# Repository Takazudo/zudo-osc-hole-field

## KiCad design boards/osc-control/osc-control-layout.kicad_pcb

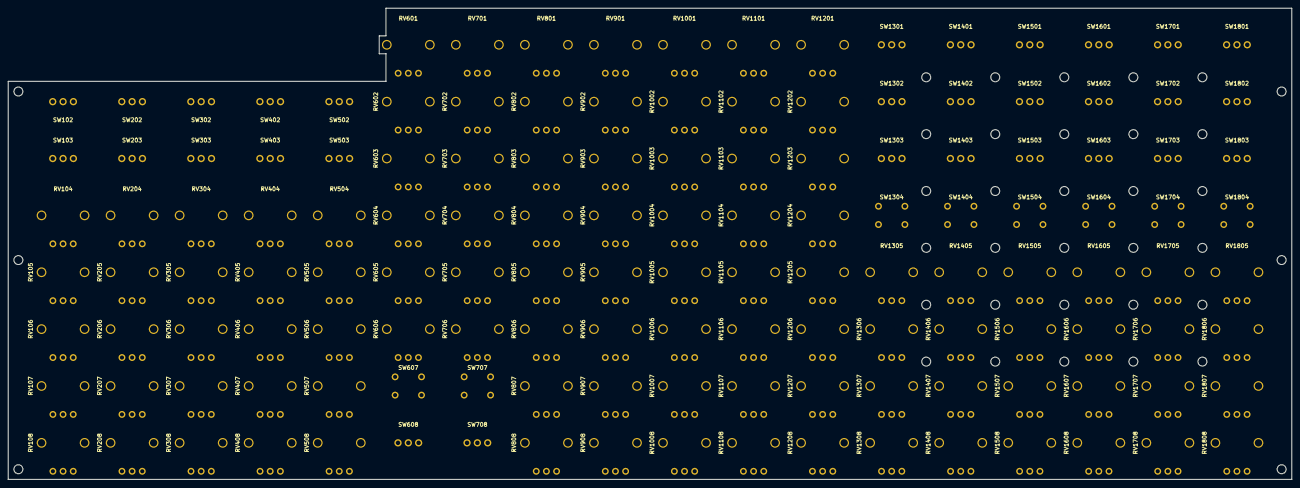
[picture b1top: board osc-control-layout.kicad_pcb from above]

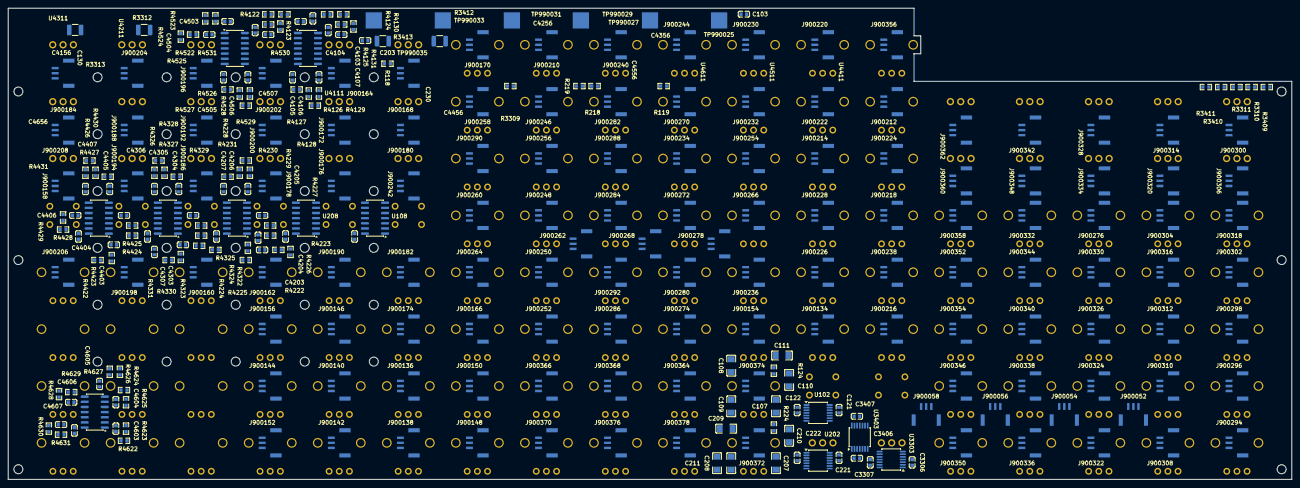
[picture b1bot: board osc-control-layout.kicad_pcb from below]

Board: 4 copper layers, 316.0 x 116.0 mm, 454 parts (279 on the bottom side), 348 nets, no tracks yet.

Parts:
C103, C203, C4104, C4105, C4106, C4107, C4204, C4205, C4206, C4207, C4304, C4305, C4306, C4307, C4404, C4405, C4406, C4407, C4504, C4505, C4506, C4507, C4604, C4605, C4606, C4607: 1e-07 F; C0603
C107, C108, C109, C110, C111, C207, C208, C209, C210, C211: 1e-07 F; C1206
C121, C122, C130, C221, C222, C230, C3306, C3307, C3406, C3407, C4156, C4256, C4356, C4456, C4556, C4656: 100 nF; C0603
C4103, C4203, C4303, C4403, C4503, C4603: 1 µF; C0603
J900052, J900054, J900056, J900058, J900134, J900136, J900138, J900140, J900142, J900144, J900146, J900148, J900150, J900152, J900154, J900156, J900158, J900160, J900162, J900164, J900166, J900168, J900170, J900172, J900174, J900176, J900178, J900180, J900182, J900184, J900186, J900188, J900190, J900192, J900194, J900196, J900198, J900200, J900202, J900204, J900206, J900208, J900210, J900212, J900214, J900216, J900218, J900220, J900222, J900224, J900226, J900228, J900230, J900232, J900234, J900236, J900238, J900240, J900242, J900244, J900246, J900248, J900250, J900252, J900254, J900256, J900258, J900260, J900262, J900264, J900266, J900268, J900270, J900272, J900274, J900276, J900278, J900280, J900282, J900284, J900286, J900288, J900290, J900292, J900294, J900296, J900298, J900300, J900302, J900304, J900306, J900308, J900310, J900312, J900314, J900316, J900318, J900320, J900322, J900324, J900326, J900328, J900330, J900332, J900334, J900336, J900338, J900340, J900342, J900344, J900346, J900348, J900350, J900352, J900354, J900356, J900358, J900360, J900362, J900364, J900366, J900368, J900370, J900372, J900374, J900376, J900378: BM03B-GHS-TBT(LF)(SN); JST_GH3_BM_TopEntry
MH_P-OPT-2, MH_P-OPT-3, MH_P-OPT-4, MH_P-OPT-5, MH_P-OPT-6, MH_P-OPT-7, MH_P-OPT-9, MH_P-OPT-10, MH_P-OPT-11, MH_P-OPT-12, MH_P-OPT-13, MH_P-OPT-14, MH_P-OPT-16, MH_P-OPT-17, MH_P-OPT-18, MH_P-OPT-19, MH_P-OPT-20, MH_P-OPT-21, MH_P-OPT-23, MH_P-OPT-24, MH_P-OPT-25, MH_P-OPT-26, MH_P-OPT-27, MH_P-OPT-28, MH_P-OPT-30, MH_P-OPT-31, MH_P-OPT-32, MH_P-OPT-33, MH_P-OPT-34, MH_P-OPT-35: NPTH mounting hole
MH_P-SUP-1, MH_P-SUP-2, MH_P-SUP-3, MH_P-SUP-4, MH_P-SUP-5, MH_P-SUP-6: NPTH mounting hole
R118, R218, R4122, R4124, R4126, R4128, R4130, R4222, R4224, R4226, R4228, R4230, R4322, R4324, R4326, R4328, R4330, R4422, R4424, R4426, R4428, R4430, R4522, R4524, R4526, R4528, R4530, R4622, R4624, R4626, R4628, R4630: 10000 Ω; R0603
R119, R219, R4123, R4125, R4127, R4129, R4131, R4223, R4225, R4227, R4229, R4231, R4323, R4325, R4327, R4329, R4331, R4423, R4425, R4427, R4429, R4431, R4523, R4525, R4527, R4529, R4531, R4623, R4625, R4627, R4629, R4631: 1000 Ω; R0603
R124, R224: 2200 Ω; R0603
R3309, R3310, R3409, R3410: 2.2 kΩ; R0603
R3311, R3411: 10 MΩ; R0603
R3312, R3313, R3412, R3413: 499 Ω; R_1210_3225Metric
RV104, RV105, RV107, RV204, RV205, RV207, RV304, RV305, RV307, RV404, RV405, RV407, RV504, RV505, RV507, RV601, RV602, RV605, RV701, RV702, RV705, RV801, RV802, RV805, RV907, RV908, RV1106, RV1107, RV1108, RV1206, RV1305, RV1306, RV1308, RV1405, RV1406, RV1408, RV1505, RV1506, RV1508, RV1605, RV1606, RV1608, RV1705, RV1706, RV1708, RV1805, RV1806, RV1808: PTV09A-4020F-B104; PTV09A-4020F
RV106, RV108, RV206, RV208, RV306, RV308, RV406, RV408, RV506, RV508, RV603, RV604, RV606, RV703, RV704, RV706, RV803, RV804, RV806, RV901, RV902, RV903, RV904, RV905, RV906, RV1001, RV1002, RV1003, RV1004, RV1005, RV1006, RV1007, RV1008, RV1101, RV1102, RV1103, RV1104, RV1105, RV1201, RV1202, RV1203, RV1204, RV1205, RV1207, RV1208, RV1307, RV1407, RV1507, RV1607, RV1707, RV1807: PTV09A-4020F-B103; PTV09A-4020F
RV807, RV808: PTV09A-4020F-B504; PTV09A-4020F
SW102, SW202, SW302, SW402, SW502, SW608, SW708, SW1302, SW1303, SW1402, SW1403, SW1502, SW1503, SW1602, SW1603, SW1702, SW1703, SW1802, SW1803: 2MS1T1B1M2QES-5; Toggle_Dailywell_2MS_T1B1M2
SW103, SW203, SW303, SW403, SW503, SW1301, SW1401, SW1501, SW1601, SW1701, SW1801: 2MS3T1B1M2QES; Toggle_Dailywell_2MS_T1B1M2
SW607, SW707, SW1304, SW1404, SW1504, SW1604, SW1704, SW1804: B3F-1020; Button_Omron_B3F_6x6_P6.5x4.5
TP990025, TP990027, TP990029, TP990031, TP990033, TP990035: LOAD WIRE SOLDER LAND; LoadWireTerminal_4x4mm
U102, U202, U3303, U3403: OPA4197IPWR; TSSOP-14_4.4x5mm_P0.65mm
U108, U208, U4111, U4211, U4311, U4411, U4511, U4611: SN74HC14DR; SOIC-14_3.9x8.7mm_P1.27mm

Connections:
+5V: C130.1, C230.1, C4156.1, C4256.1, C4356.1, C4456.1, C4556.1, C4656.1, R118.1, R218.1, R4122.1, R4124.1, R4126.1, R4128.1, R4130.1, R4222.1, R4224.1, R4226.1, R4228.1, R4230.1, R4322.1, R4324.1, R4326.1, R4328.1, R4330.1, R4422.1, R4424.1, R4426.1, R4428.1, R4430.1, R4522.1, R4524.1, R4526.1, R4528.1, R4530.1, R4622.1, R4624.1, R4626.1, R4628.1, R4630.1, TP990029.1, U108.14, U208.14, U4111.14, U4211.14, U4311.14, U4411.14, U4511.14, U4611.14
+12V: C122.1, C222.1, C3306.1, C3406.1, TP990025.1, U102.4, U202.4, U3303.4, U3403.4
-12V: C121.1, C221.1, C3307.1, C3407.1, TP990027.1, U102.11, U202.11, U3303.11, U3403.11
AGND: C103.2, C107.2, C108.2, C109.2, C110.2, C111.2, C121.2, C122.2, C130.2, C203.2, C207.2, C208.2, C209.2, C210.2, C211.2, C221.2, C222.2, C230.2, C3306.2, C3307.2, C3406.2, C3407.2, C4103.2, C4104.2, C4105.2, C4106.2, C4107.2, C4156.2, C4203.2, C4204.2, C4205.2, C4206.2, C4207.2, C4256.2, C4303.2, C4304.2, C4305.2, C4306.2, C4307.2, C4356.2, C4403.2, C4404.2, C4405.2, C4406.2, C4407.2, C4456.2, C4503.2, C4504.2, C4505.2, C4506.2, C4507.2, C4556.2, C4603.2, C4604.2, C4605.2, C4606.2, C4607.2, C4656.2, J900052.2, J900054.2, J900056.2, J900058.2, J900134.2, J900136.2, J900138.2, J900140.2, J900142.2, J900144.2, J900146.2, J900148.2, J900150.2, J900152.2, J900154.2, J900156.2, J900158.2, J900160.2, J900162.2, J900164.2, J900166.2, J900168.2, J900170.2, J900172.2, J900174.2, J900176.2, J900178.2, J900180.2, J900182.2, J900184.2, J900186.2, J900188.2, J900190.2, J900192.2, J900194.2, J900196.2, J900198.2, J900200.2, J900202.2, J900204.2, J900206.2, J900208.2, J900210.2, J900212.2, J900214.2, J900216.2, J900218.2, J900220.2, J900222.2, J900224.2, J900226.2, J900228.2, J900230.2, J900232.2, J900234.2, J900236.2, J900238.2, J900240.2, J900242.2, J900244.2, J900246.2, J900248.2, J900250.2, J900252.2, J900254.2, J900256.2, J900258.2, J900260.2, J900262.2, J900264.2, J900266.2, J900268.2, J900270.2, J900272.2, J900274.2, J900276.2, J900278.2, J900280.2, J900282.2, J900284.2, J900286.2, J900288.2, J900290.2, J900292.2, J900294.2, J900296.2, J900298.2, J900300.2, J900302.2, J900304.2, J900306.2, J900308.2, J900310.2, J900312.2, J900314.2, J900316.2, J900318.2, J900320.2, J900322.2, J900324.2, J900326.2, J900328.2, J900330.2, J900332.2, J900334.2, J900336.2, J900338.2, J900340.2, J900342.2, J900344.2, J900346.2, J900348.2, J900350.2, J900352.2, J900354.2, J900356.2, J900358.2, J900360.2, J900362.2, J900364.2, J900366.2, J900368.2, J900370.2, J900372.2, J900374.2, J900376.2, J900378.2, R3311.2, R3411.2, RV106.1, RV107.1, RV108.1, RV206.1, RV207.1, RV208.1, RV306.1, RV307.1, RV308.1, RV406.1, RV407.1, RV408.1, RV506.1, RV507.1, RV508.1, RV601.1, RV602.1, RV603.1, RV604.1, RV605.1, RV606.1, RV701.1, RV702.1, RV703.1, RV704.1, RV705.1, RV706.1, RV801.1, RV802.1, RV803.1, RV804.1, RV805.1, RV806.1, RV901.1, RV902.1, RV903.1, RV904.1, RV905.1, RV906.1, RV907.1, RV1001.1, RV1002.1, RV1003.1, RV1004.1, RV1005.1, RV1006.1, RV1007.1, RV1008.1, RV1101.1, RV1102.1, RV1103.1, RV1104.1, RV1105.1, RV1106.1, RV1107.1, RV1201.1, RV1202.1, RV1203.1, RV1204.1, RV1205.1, RV1206.1, RV1207.1, RV1208.1, RV1305.1, RV1306.1, RV1307.1, RV1405.1, RV1406.1, RV1407.1, RV1505.1, RV1506.1, RV1507.1, RV1605.1, RV1606.1, RV1607.1, RV1705.1, RV1706.1, RV1707.1, RV1805.1, RV1806.1, RV1807.1, SW102.1, SW202.1, SW302.1, SW402.1, SW502.1, SW607.1, SW607.2, SW707.1, SW707.2, SW1301.2, SW1302.2, SW1303.2, SW1304.1, SW1304.2, SW1401.2, SW1402.2, SW1403.2, SW1404.1, SW1404.2, SW1501.2, SW1502.2, SW1503.2, SW1504.1, SW1504.2, SW1601.2, SW1602.2, SW1603.2, SW1604.1, SW1604.2, SW1701.2, SW1702.2, SW1703.2, SW1704.1, SW1704.2, SW1801.2, SW1802.2, SW1803.2, SW1804.1, SW1804.2, TP990031.1, TP990033.1, TP990035.1, U102.10, U102.12, U108.3, U108.5, U108.7, U108.9, U108.11, U108.13, U202.10, U202.12, U208.3, U208.5, U208.7, U208.9, U208.11, U208.13, U3303.5, U3303.10, U3303.12, U3403.5, U3403.10, U3403.12, U4111.7, U4111.13, U4211.7, U4211.13, U4311.7, U4311.13, U4411.7, U4411.13, U4511.7, U4511.13, U4611.7, U4611.13
X0B4A0A5D45814E9D95C7: U3303.13, U3303.14
X0B332CC3F3D75834394B: J900344.1, RV404.3, RV405.3, RV407.3
X0B475DAB16A59C025E35: J900170.1, U4111.10
X0C487389EDA1C803A833: J900304.3, SW102.2
X00D3BCB5E0AFD29A84DF: J900314.1, SW203.1
X0E3CA1A11E5FE92DB152: J900242.1, U108.2
X0F98EC836B304857ABC5: C4404.1, R4425.2, U4411.3
X01A05DBEFB68471D9824: J900186.1, U4311.10
X1A9EF65F44F4B29DE1DC: J900368.1, RV1207.3
X1B3E855D0EAF37C63927: J900326.3, RV306.3
X1B80C209713652D469B7: J900328.3, SW302.3
X1B787BB4D565EE8CF824: R4226.2, R4227.1, SW1401.3
X1C49E274E70449E3D265: R3309.2, SW608.3
X1C545F78A9EEA47275D3: J900148.3, RV1608.2
X1CB7E660D7B486B8C4E6: J900056.1, R3313.2
X1D7C13EF0F0429C157CA: J900212.3, RV603.2
X1DA6F66C3F8A34A27A5F: U3403.6, U3403.7
X1DA464D505A944A51104: J900360.1, RV508.3
X1E5E726E8BFBF2C8D7CB: J900198.3, RV1706.2
X1EA7A310545B3EA7B872: C4603.1, R4623.2, U4611.1
X1F3BE2B0C54B7392AAD2: J900214.1, RV602.2
X1FFDC49339C7C2982F1A: J900256.1, RV1102.2
X2B2FD6CD1D1554A8B31B: J900164.1, U4111.4
X2BCD7805C65AE3992EDF: R4628.2, R4629.1, SW1802.3
X2CA281339CB17909B79A: J900332.1, RV308.3
X02CB8FF55279DAA45A09: J900196.1, U4511.4
X2D597327EED2D1A7509E: J900162.3, RV1808.1
X2DAE1746253A01B64F3C: J900346.1, RV408.3
X2F4053E8598569E6249E: J900362.3, SW503.2
X3A090CBB9D59BF6BFA74: C103.1, R119.2, U108.1
X3AACF3FE67214DD30896: R4422.2, R4423.1, SW1604.3, SW1604.4
X3B8BA61DD852C09F9593: J900182.1, RV1505.2
X3B24EF7B17B8D143C1C5: J900058.3, R3413.2
X3BE215420217265BBCC4: J900330.3, RV304.1, RV305.1
X3C4EB2F54BEF66A2BDCD: J900372.1, RV908.2
X3C30CF4F46CC9EAA54FD: C4405.1, R4427.2, U4411.5
X3CB093BB7419E86B97DC: J900198.1, RV1705.2
X3D9DB9D8CDF65F493A37: J900208.1, U4611.6
X3DAC76D7A558264A3F1B: J900260.3, RV1204.3
X3F9931ACD1A8A527BDB6: J900274.3, RV906.2
X3FCBFC999FCAA257D324: R4622.2, R4623.1, SW1804.3, SW1804.4
X4AD789F56C4006DE7DA9: J900264.1, RV1206.2
X4C73DFC1A892FFD889F5: C4205.1, R4227.2, U4211.5
X4E9DA5171986B7A73694: J900292.1, RV1004.2
X04EB6B3DC069E08BFECF: J900310.3, RV207.2
X4F82C77EF7F47F31A68A: J900306.3, SW103.2
X5AC892F0D8CDA44E7E18: J900322.3, RV308.2
X05B3B6DFB0CF591143F1: J900374.1, RV907.2
X5BC1C28EAF5D67603036: J900340.3, RV406.3
X5BDE0CC9A020C6F2E113: J900136.3, RV1308.3
X5E1E2BAA433858C2BF43: U202.8, U202.9
X5EE2EC8E69809DDC2E3E: C4306.1, R4329.2, U4311.9
X5FA328E898DBF1047AD9: J900140.3, RV1407.3
X06C7F5D4F085BBED1E86: J900370.3, RV1108.1
X6C227D1A4FFD615CE3B4: J900152.1, RV1608.3
X6EAF3E6A330509674504: R4426.2, R4427.1, SW1601.3
X6F1E82B9DD7E6011E5A7: U3403.8, U3403.9
X7B5C74E08F15CF029DD6: J900256.3, RV1106.3
X7B7BDD1C1DB4BA20302F: C4106.1, R4129.2, U4111.9
X7B6418A02124BE1D6A53: J900346.3, SW402.2
X7CA4825DF75BA1068B88: J900312.3, RV206.3
X7DF116D877C176D3E3C1: R4230.2, R4231.1, SW1403.3
X7EC00F55D7B5A706ABE8: J900160.1, RV1807.2
X7EED3C2496125C7B4C01: J900226.3, RV704.2
X7FF164FB414EE3E69E00: J900348.1, SW403.3
X8A7D7D29E8DC52F3CE4A: J900206.1, RV1805.2
X8A58565164C7AD5DB771: J900210.3, U4611.2
X08AB1FE396D2383E44F4: J900210.1, U4611.10
X8B9429ACCBF48C55D3C2: C4607.1, R4631.2, U4611.11
X8BE7E102E23D65C3BAE8: C4304.1, R4325.2, U4311.3
X8D47F4038AE6E42915B2: J900300.3, SW102.3
X8D097FC3EE080878BFAC: J900234.3, RV805.2
X8EE69A8E59E4947794DE: R224.2, RV808.1
X8F338CC60323B9942D2C: C4103.1, R4123.2, U4111.1
X8FFBDC9C42EC02C29B2F: J900278.1, RV902.2
X9A2A689D1C741BE6AFED: J900280.1, RV904.2
X9A343D229ADA66A13020: J900176.3, RV1405.3, RV1406.3
X9A815A035049F63C9E88: J900244.1, U208.2
X9B0D87C92BF046274E53: U202.13, U202.14
X9C285D3C07BA239ADB72: J900324.3, RV307.2
X9D8BBA8996899EAF9E11: R4424.2, R4425.1, SW1601.1
X9D084A84DCD90DC3DD20: R218.2, R219.1, SW707.3, SW707.4
X9D0800DA698428AE22E5: J900366.1, RV1107.2
X9F7D653AF2B7E248C875: J900232.1, RV801.2
X9F175A89D847BE3F6D46: J900226.1, RV706.2
X9F47443B516E90FF872D: J900302.3, RV104.1, RV105.1
X10EF5F2EA06ABBC332A2: J900146.1, RV1507.3
X11FD029782B329BAC0F5: J900192.1, U4411.6
X14E3C0C55CB1C4A95F24: J900286.1, RV1005.3
X17D4FDC40CFD180B1BD2: J900168.1, U4111.6
X21BEBE4AB581C385D0B8: R4130.2, R4131.1, SW1303.3
X24E3C16307B2FAA35477: J900222.3, RV703.2
X27B80377B6C412E86A02: J900286.3, RV1006.2
X27C28FDCAA9450E228E6: J900272.1, RV903.3
X32DCB2CFC06DB06B386F: R4228.2, R4229.1, SW1402.3
X33CA5B7F1AD1677C7737: J900254.1, RV1103.2
X0034A88A682FE94105E3: R224.1, U202.1, U202.2
X35C328C82C2EDBE601ED: J900182.3, RV1506.2
X35E86F1B470C2BA578A1: J900354.3, RV506.3
X36A08C40CCEBB620DE23: R3412.2, R3413.1
X37C0D40E8793B92EA1B7: J900330.1, RV304.3, RV305.3, RV307.3
X37DEB0D3B35ED7C3B732: J900054.1, R3309.1
X41B88AA72B8A732B279A: J900316.3, RV204.1, RV205.1
X44CC9CDFCD3CBADF5D00: J900298.1, RV105.2
X45AEDA7EA8DE3AE9B3ED: J900162.1, RV1808.3
X47A1F716E3FE17CD7494: J900142.3, RV1408.1
X47F88BF45C5E2E011545: J900218.3, RV606.3
X48EC6FDDD901F447E0D7: J900138.3, RV1408.2
X48FE18B13B6BACB7D2F3: J900150.1, RV1607.2
X53E6848A29A94622ABBC: J900332.3, SW302.2
X056B4CC99FD47B93EDCC: J900224.3, RV705.2
X57F83BC709B895AAD727: R4430.2, R4431.1, SW1603.3
X59AF92DF21D7A5330CF8: C4207.1, R4231.2, U4211.11
X61C55F327009ADDFA763: J900348.3, SW403.2
X65AE667238FA95A8F74F: J900338.3, RV407.2
X65E4D2E1B5D6DE7493A2: J900242.3, U102.3
X65EF910626D86173FCAE: R3312.1, U3303.1, U3303.2
X67D9684AF7D381D085BB: J900150.3, RV1607.3
X69F956D2CD0D8F7D7812: J900184.3, RV1505.3, RV1506.3
X70DC76294A6404803334: J900282.1, RV1001.3
X70FF44125622536BA5C7: J900052.3, U202.6, U202.7
X73DBDA5E90E6EB5C88CC: J900160.3, RV1807.3
X73DCD6567A68738230C2: C4605.1, R4627.2, U4611.5
X74FE612A599C88EF9232: J900202.3, U4511.2
X76CBC2A15ACB37487709: J900250.3, RV1104.2
X76D81676C30D329CC9B5: J900288.3, RV1003.2
X77E7E88701ED796DE532: C107.1, C108.1, C109.1, C110.1, C111.1, RV807.2, RV807.3, U102.5
X78C1702B66BDCEBC593E: J900276.3, RV903.2
X79AAE9302AB11BB4C973: J900144.3, RV1507.2
X80E184FE788FFBE8EA58: J900378.3, RV908.1
X84A4FF7293A182F02A4A: R4524.2, R4525.1, SW1701.1
X85E738180F5C70F1A457: J900222.1, RV701.2
X89D5E3CA45DE92E8F54F: J900192.3, RV1605.3, RV1606.3
X91AB2074CD577F2FF2D8: J900248.1, RV1103.3
X92D58D65DA2819F30731: J900216.3, RV604.2
X92F7EC5BF13E7E12AB51: J900320.1, SW203.3
X93B85254A7CAE093D017: J900368.3, RV1208.3
X94AE1057F6F6F403AA12: R4522.2, R4523.1, SW1704.3, SW1704.4
X97ED0B30E9679E8FC3C2: J900218.1, RV603.3
X110EF417EBA43801D3CA: J900298.3, RV106.3
X130E2D2473EEC58833A8: J900184.1, U4311.6
X144C922A18FA87072963: J900350.1, RV506.2
X146B2E086CDC142CF6D6: J900356.1, SW503.1
X214ED5A8892039CF8AA7: J900168.3, RV1305.3, RV1306.3
X387EC52CA3999BB128B1: J900244.3, U202.3
X476A0733582A82F0AEB8: C4307.1, R4331.2, U4311.11
X489F21AF98C74FBB046F: J900252.3, RV1105.2
X494A69F57398E0094B88: J900318.3, SW202.2
X514AF48BBD9C212363F8: J900134.3, RV1307.2
X547DC548216A545CE445: R3310.2, SW608.1
X567D5C752D604876B08A: J900276.1, RV901.2
X595CFB34B72941F8A5A8: C203.1, R219.2, U208.1
X599D6F008ACD4AF9DBB6: J900240.3, RV804.3
X652F7E92722B07CC611F: C4604.1, R4625.2, U4611.3
X664ED05EACC39FA0A717: C4204.1, R4225.2, U4211.3
X665F99D69A5D3F2A216F: J900246.3, RV1102.3
X695F4CDA5CB45DBBBA8D: J900364.1, RV1108.2
X741DF1C2056440887FCB: J900312.1, RV205.2
X763E77DF6D4025E687FA: J900300.1, SW103.1
X849EE8C41DE7382BA070: J900234.1, RV802.2
X927D723306618B2FA404: R4526.2, R4527.1, SW1701.3
X937C92F685B83C082055: J900366.3, RV1207.2
X1080B5575AB1BB1A0248: J900314.3, SW202.3
X1675C414E0F088C8B0F2: J900376.3, RV1008.3
X1897FA4CC6D2320FE9FC: R4530.2, R4531.1, SW1703.3
X2116EAF991E4FD59E329: J900052.1, U102.6, U102.7
X2235AA409133311006A2: J900268.3, RV1206.3
X2781F3EA18C148791B18: J900202.1, U4511.10
X2842A95258EB703DE67C: J900302.1, RV104.3, RV105.3, RV107.3
X3878A543A34D0072B9DD: J900260.1, RV1203.3
X03899EF77CFB15DF4250: J900306.1, SW103.3
X3977E5498D871E0002C5: C4105.1, R4127.2, U4111.5
X4838A855AA88CEFB49D1: J900354.1, RV505.2
X5270B2A325DCFA73F65F: J900236.1, RV806.2
X5585D1E58EEAC7D5FB9D: C4303.1, R4323.2, U4311.1
X05736A904C0279F1CE63: J900148.1, RV1508.1
X5768B5A3D3AC9B88DB51: J900352.3, RV507.2
X5786DA3A2B61D0A46B7F: J900214.3, RV605.2
X6598D7A6A04405CC9D96: J900178.1, U4211.10
X6641CDA99062907B3A69: J900322.1, RV306.2
X07234E2FF52429093754: J900284.1, RV1003.3
X7598FF643F131BC55CC1: U102.13, U102.14
X8075E891B07A88D4D9CB: J900374.3, RV1007.2
X8314A000574C61D85A46: C4206.1, R4229.2, U4211.9
X8371D5E9C0B97F4C6EC4: R4528.2, R4529.1, SW1702.3
X9480A1F10120402F93CC: C4104.1, R4125.2, U4111.3
X9767C64E126DEDB6653C: J900212.1, RV601.2
X9791E4C8B176990128D8: J900196.3, U4511.8
X12526D06AC7BB87D9196: J900190.1, RV1605.2
X15938C42644C2F3EFBEE: J900310.1, RV204.2
X17743E5166C7DE548F70: J900324.1, RV304.2
X40646DB4DABEB9C85A07: J900140.1, RV1407.2
X43247E56B6D8AFCD6E84: U3303.6, U3303.7
X46270C135ACB2EB383FC: J900268.1, RV1202.2
X50598DC0C3D8C362685E: J900358.3, RV504.1, RV505.1
X57434BF4C4A2400D5FF7: J900200.1, U4511.6
X58381FC52FCDDA9B0131: J900248.3, RV1104.3
X69343E2C6D875EFAA724: R4630.2, R4631.1, SW1803.3
X71410CF334ACBB57EDFF: R4326.2, R4327.1, SW1501.3
X81320A62027112B50CB2: J900220.3, RV604.3
X98302BA4179BABC520A9: R4626.2, R4627.1, SW1801.3
X275914F8D0058F71EFF0: J900304.1, RV108.3
X461891EDAD0B2EB306D7: J900342.3, SW402.3
X479764B836FB7BB3EF48: J900204.1, U4611.4
X594671D4E0DDE8EDD9FF: J900176.1, U4211.6
X649135E2E9A5ED5B0367: J900292.3, RV1006.3
X699048DF1C17BB355894: J900294.3, RV108.2
X826169EDE09D7A95D8A3: J900262.1, RV1205.3
X965884E569C2BD8409A5: J900156.3, RV1708.3
X2620246FAC3FF931C427: J900250.1, RV1105.3
X6158489D0D822E09DE71: C4606.1, R4629.2, U4611.9
X7232057F47316092B5DF: J900340.1, RV405.2
X8516142BE3CF69C34E20: J900156.1, RV1707.3
X52268074E547F37C1BDF: J900320.3, SW203.2
X69557299DAC5668C77C1: C4504.1, R4525.2, U4511.3
X81661675DED6E82682D1: J900204.3, U4611.8
X83505917C4B7487D1CE9: J900228.1, RV703.3
X85312435D1384AC142A0: C4505.1, R4527.2, U4511.5
X93401982C2F89B584227: J900266.1, RV1203.2
X532980813DED35791CED: J900224.1, RV702.2
X14489165961EB95B7CC4: J900188.1, U4411.4
XA1D49D92DDF2AA0DEFCB: R4324.2, R4325.1, SW1501.1
XA5F650FE3E97CBF41AB3: J900296.1, RV104.2
XA16BE2D8C2D07015E3FC: J900246.1, RV1101.3
XA019E807E2A752FFC687: J900328.1, SW303.1
XA82AFE6CDE755FEB4702: J900220.1, RV601.3, RV602.3, RV605.3
XA96E8D0F184A39DEE620: J900352.1, RV504.2
XA585181D0B9DE3587445: J900290.3, RV1005.2
XA298250074404F530DD4: J900262.3, RV1204.2
XAABE3B2B73AE6287C63B: J900190.3, RV1606.2
XAB90894E398C3C7E5F74: J900154.3, RV1707.2
XABCED8BE76EFD3D1772D: C4507.1, R4531.2, U4511.11
XABD60A45AAAC75EB8951: J900238.1, RV803.3
XAC9F56A148C41BDAFC02: J900370.1, RV1107.3, RV1108.3
XAD2A38741611D509A34E: J900258.3, RV1202.3
XADB906B43917B481E867: J900296.3, RV107.2
XAE2CAC8AF4B937F6AE8F: J900372.3, RV1008.2
XB2F3DB94BF7BF9B0FAA0: J900194.3, U4411.2
XB2F6FC20D1E21C4537F7: J900216.1, RV606.2
XB4AA499139E7DBBB1BBF: U3403.13, U3403.14
XB6FA1BCBBFA3EEA95431: R4624.2, R4625.1, SW1801.1
XB7F3177099060F5D98BF: J900134.1, RV1308.2
XB08FE271FD1E7E3F3792: J900258.1, RV1201.3
XB23B6C7A8BC4FC5604FF: J900054.3, R3310.1
XB26BE8615EDC7481E388: J900378.1, RV907.3, RV908.3
XB28FA53CC1E9A761BD1C: J900186.3, U4311.2
XB77A49BB412844B458C3: J900284.3, RV1004.3
XB528E61191525CCF0307: J900334.3, SW303.2
XB831DD9554502BE87093: C4506.1, R4529.2, U4511.9
XB1740D19174FCDC57A89: J900356.3, SW502.3
XB9604987375065EFAB29: R4122.2, R4123.1, SW1304.3, SW1304.4
XBB7C344851AF8D0601AC: J900316.1, RV204.3, RV205.3, RV207.3
XBB47CF2D4959FF3CCA75: J900136.1, RV1307.3
XBCA4688CC73D43650238: J900164.3, U4111.8
XBCECD88113B6B382C9D6: R3311.1, SW608.2, U3303.3
XBD6357A0B75FD46712BB: R4330.2, R4331.1, SW1503.3
XBE98C64E37574FAA5054: J900350.3, RV508.2
XC1A8C7D75E8208D95A79: R124.1, U102.1, U102.2
XC6A7664726BAFEE0BCFA: J900158.1, RV1708.1
XC7F5BDC04F0481121BA1: R4128.2, R4129.1, SW1302.3
XC22E458B0CC1481C514F: J900208.3, RV1805.3, RV1806.3
XC57F7B82CBD19A62D640: J900174.1, RV1405.2
XC88BD03BBA8813E56671: J900058.1, R3410.1
XC394C67B39CCAC7BCAC2: J900180.1, U4311.4
XC6592B5E19554E448150: C4503.1, R4523.2, U4511.1
XC19387F5B49A211AD2BD: J900230.1, RV701.3, RV702.3, RV705.3
XC36004EDAFB86F42B8A0: J900230.3, RV704.3
XC90878538D724AB44D09: U102.8, U102.9
XCC667F25662CC0A86294: J900172.3, U4211.8
XCC1350026597CEE286BE: J900308.1, RV206.2
XCCCAB78611B006E208B7: J900166.1, RV1305.2
XCD73253CE48AB875471C: J900178.3, U4211.2
XCDE0D0AB6372C2F8FE76: C4305.1, R4327.2, U4311.5
XCE6BC31263AA083C91E8: J900188.3, U4411.8
XCED786ED54CE8360C1D2: U3303.8, U3303.9
XCEE2A45C975E1AFE65D9: J900336.3, RV408.2
XCFFE7511BC889FE8CD18: J900254.3, RV1101.2
XD0AB63C429782D345CFA: J900266.3, RV1201.2
XD0AC980CC381CB2DED7A: J900278.3, RV905.2
XD0AEDF2201C438BC951F: J900280.3, RV906.3
XD1EDEFA1D77DEDD194A8: R3412.1, U3403.1, U3403.2
XD2D99513A5A51F131C78: J900138.1, RV1308.1
XD35CC6F950919CDBDA22: J900282.3, RV1002.3
XD305DDFAE7E0616793A4: J900326.1, RV305.2
XD925A488BFF88EC55A0E: J900180.3, U4311.8
XD51322DA5CCAF0966272: J900334.1, SW303.3
XD495321DB3DAE206B30C: R4428.2, R4429.1, SW1602.3
XD4682362CD25092A347B: J900308.3, RV208.2
XD724017984C2562351FC: J900142.1, RV1408.3
XDC1D2B49BF3116ED3DE3: C4407.1, R4431.2, U4411.11
XDC689FCDF5CBA0DA1EF3: J900288.1, RV1001.2
XDEC65E1C2FBB68F45A66: J900238.3, RV806.3
XDF62172BE5B25A600C9B: J900274.1, RV905.3
XE2B9B937D5CAF54AD63F: J900146.3, RV1508.3
XE3CCFA14F6E3DCF3F5F1: C207.1, C208.1, C209.1, C210.1, C211.1, RV808.2, RV808.3, U202.5
XE4E1513DE79627D3BBC3: J900206.3, RV1806.2
XE5EBE89E3604C69EA63D: R4126.2, R4127.1, SW1301.3
XE31F05877B8C46E4CC67: R4224.2, R4225.1, SW1401.1
XE50F7010B563D9E69D06: J900174.3, RV1406.2
XE53E68F96134553749FD: J900360.3, SW502.2
XE57A4DF41E8F2F4A1ABF: R4124.2, R4125.1, SW1301.1
XE70CD3179D3A13387B23: J900252.1, RV1106.2
XE15497AEEB69BDAA0843: J900240.1, RV801.3, RV802.3, RV805.3
XE41711BCCEBB68517871: J900154.1, RV1708.2
XE2766944E33E2DEBD272: R3409.2, SW708.3
XE5866228E5A533B6E0A9: J900362.1, SW503.3
XE94499060CE17305BDE7: R4322.2, R4323.1, SW1504.3, SW1504.4
XEA6E5859150D0A15C748: J900376.1, RV1007.3
XEA71DBF9A3F5D1DD1ED4: J900358.1, RV504.3, RV505.3, RV507.3
XEB38D85612513E2B4A8F: J900232.3, RV803.2
XEB97E29642F2FC671EF7: C4406.1, R4429.2, U4411.9
XEBD42A167753CD6F1F23: J900172.1, U4211.4
XEC29CCFBAB51F823DB99: J900336.1, RV406.2
XECF2E811656C746385DF: J900158.3, RV1808.2
XED9D669DEDB8C275FBBC: J900152.3, RV1608.1
XED165ED96D75C15A85C4: J900200.3, RV1705.3, RV1706.3
XEEF5A855E362B4B0F6B0: J900144.1, RV1508.2
XEF027B8766AA5FE667C7: C4107.1, R4131.2, U4111.11
XF0C367296DC4E1E8E437: R124.2, RV807.1
XF0DC26E7D2B4314CF41F: C4203.1, R4223.2, U4211.1
XF1EBD465D8DD5809EB46: J900318.1, RV208.3
XF1FB9B9571EC724C1984: R4328.2, R4329.1, SW1502.3
XF5B9E6F0AF41CB8B8516: J900338.1, RV404.2
XF5F945E041AE420297D7: J900194.1, U4411.10
XF6BF97BFAAAC54218A4D: C4403.1, R4423.2, U4411.1
XF6C8E900470ABEB1A926: R3411.1, SW708.2, U3403.3
XF7A09A49BFFF2E1410A0: J900272.3, RV904.3
XF11E66144A76406E10FB: R118.2, R119.1, SW607.3, SW607.4
XF54E77C0E32924534D70: J900170.3, U4111.2
XF60FF06731037B7D38F4: R3312.2, R3313.1
XF64CE2464C26725B93EA: J900264.3, RV1205.2
XF66CDA4C7BD039CA904A: J900364.3, RV1208.2
XF73FE32FB15AF76B6C21: J900290.1, RV1002.2
XF98E7C4AE59913C0EB61: J900270.3, RV902.3
XF114FCC8B218E1013F4D: J900228.3, RV706.3
XF195CC86A82C6BA38868: J900270.1, RV901.3
XF843AB8415743DF881C6: R3410.2, SW708.1
XF2827D8A0A013B839CAA: J900344.3, RV404.1, RV405.1
XF33834373CE4E1458596: J900056.3, R3409.1
XFACEAC4AD4236AE2EDC7: J900236.3, RV804.2
XFEC100AF3DB43E9BF8BD: J900342.1, SW403.1
XFEE1B008C89F229D7744: R4222.2, R4223.1, SW1404.3, SW1404.4
XFF51449A8957A022385F: J900294.1, RV106.2
XFFE1FE953B93A0E1C890: J900166.3, RV1306.2
